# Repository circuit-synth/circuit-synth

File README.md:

# circuit-synth

Define electronic circuits in Python and generate KiCad projects (schematic +
PCB) from them.

> **This is a development fork** of [circuit-synth](https://github.com/circuit-synth/circuit-synth).
> It is not published to PyPI under this fork; install it locally (below).
> Everything documented here is verified against the code in `src/circuit_synth/`.

## What it does

You describe components and their connections in Python; circuit-synth produces
a complete KiCad project. Because the design is code, it is diffable,
version-controlled, and composable — subcircuits are just functions you call.

```python
from circuit_synth import circuit, Component, Net

@circuit(name="Power_Supply")
def power_supply(vin, vout, gnd):
    """5V -> 3.3V linear regulator with decoupling."""
    reg = Component(
        symbol="Regulator_Linear:AMS1117-3.3",
        ref="U",
        footprint="Package_TO_SOT_SMD:SOT-223-3_TabPin2",
    )
    cin  = Component(symbol="Device:C", ref="C", value="10uF")
    cout = Component(symbol="Device:C", ref="C", value="22uF")

    reg["VI"] += vin
    reg["VO"] += vout
    reg["GND"] += gnd
    cin[1]  += vin;  cin[2]  += gnd
    cout[1] += vout; cout[2] += gnd

@circuit(name="Main")
def main():
    vbus, vcc, gnd = Net("VBUS"), Net("VCC_3V3"), Net("GND")
    power_supply(vbus, vcc, gnd)

if __name__ == "__main__":
    main().generate_kicad_project("my_board")   # -> my_board/*.kicad_sch, *.kicad_pcb
```

## Install (development fork)

```bash
git clone <this fork's url> circuit-synth
cd circuit-synth
uv sync                     # create the environment from uv.lock
uv run pytest               # sanity-check the install
```

Requirements:
- Python 3.12+
- `uv` (environment/build; the project uses setuptools + uv, not poetry)
- A KiCad install with `kicad-cli` on PATH. The fork's active work targets
  KiCad 10; `kicad-cli` is used for BOM/PDF/Gerber export.

## Core API

Exported from `circuit_synth`: `circuit`, `Component`, `Net`, `Pin`, `Circuit`.

- `Component(symbol=..., ref=..., footprint=..., value=..., **fields)` — a KiCad
  symbol instance. Extra keywords become component fields (used in the BOM).
- `Net("NAME")` — an electrical net. Connect a pin with `component["PIN"] += net`
  (named) or `component[1] += net` (numbered).
- `@circuit(name=...)` — decorates a function into a circuit; call other
  `@circuit` functions inside it to build hierarchy.

### Generation and manufacturing outputs

Methods on the circuit object returned by a `@circuit` function:

```python
c = main()

c.generate_kicad_project(
    "my_board",
    generate_pcb=True,                 # also lay out a .kicad_pcb
    placement_algorithm="hierarchical",# or "simple"
    force_regenerate=False,            # True discards manual KiCad edits
    update_source_refs=None,           # see "Reference rewriting"
)

c.generate_bom("my_board")            # CSV BOM (kwargs: output_file, group_by, exclude_dnp, ...)
c.generate_pdf_schematic("my_board")  # PDF (kwargs: black_and_white, pages, ...)
c.generate_gerbers("my_board")        # Gerber + drill files
```

BOM/PDF/Gerber export shells out to KiCad's `kicad-cli`. See
[docs/BOM_EXPORT.md](docs/BOM_EXPORT.md), [docs/PDF_EXPORT.md](docs/PDF_EXPORT.md),
[docs/GERBER_EXPORT.md](docs/GERBER_EXPORT.md).

### Reference rewriting

When references are finalized during generation (e.g. `ref="C"` becomes
`ref="C1"`), circuit-synth can write the finalized refs back into your Python
source file, so repeated generations stay consistent. Controlled by
`update_source_refs` (default `None` = auto-update unless `force_regenerate=True`;
pass `True`/`False` to force it). It rewrites `ref=` assignments only and leaves
comments/docstrings alone.

### Round-trip (KiCad <-> Python)

Both directions exist as CLI tools: `python-to-kicad` and `kicad-to-python`. You
can generate from Python, edit in KiCad, and import back.

## Starting a project

```bash
uv run cs-new-project my_board     # scaffold a project (starter circuit + Claude tooling)
cd my_board
uv run python circuit-synth/main.py   # generate the KiCad files
```

`cs-new-project` copies the packaged `example_project` template (a `circuit-synth/`
source folder, a `.claude/` design skill, and `tools/find_symbol.py`).
`cs-bootstrap` does the same and can run `main.py` for you in one step.

## Other capabilities (real, optional)

These exist in the package; most need extra setup or network access, and are
peripheral to the core Python -> KiCad flow:

- **SPICE simulation** — `circuit.simulator()` exposes `operating_point()`,
  `ac_analysis()`, etc. (ngspice). See [docs/SIMULATION_SETUP.md](docs/SIMULATION_SETUP.md).
- **FMEA report** — `cs-fmea my_circuit.py` generates a reliability report. See
  [docs/FMEA_GUIDE.md](docs/FMEA_GUIDE.md).
- **Component sourcing** — JLCPCB/DigiKey/SnapEDA search via the `jlc-fast` CLI
  and `circuit_synth.manufacturing.find_parts(...)`. DigiKey/SnapEDA need API
  keys (`cs-setup-digikey-api`, `cs-setup-snapeda-api`); JLCPCB search needs
  network access.

## Claude Code integration

The design loop is driven by skills and tools (not custom slash commands):

- **`new-kicad-project` skill** — bootstrap a new project.
- **`design-circuit` skill** — the design → verify → generate loop, including
  symbol/footprint lookup via `tools/find_symbol.py`.
- **kicad-sch-api MCP server** — programmatic read/write of `.kicad_sch` files.

Verify symbols/footprints with `tools/find_symbol.py` rather than trusting a
static list — names vary by KiCad version and are easy to get wrong.

## Development

```bash
uv run pytest                # tests
black src/ tests/            # format (also run by pre-commit)
isort src/ tests/
```

See [CLAUDE.md](CLAUDE.md) for the working policy (human-in-the-loop; commit
often; **no PyPI releases**) and the loop boundary contract, and
[docs/CONTRIBUTING.md](docs/CONTRIBUTING.md) / [docs/TESTING.md](docs/TESTING.md).

## Architecture

JSON is the canonical intermediate representation between Python and KiCad,
which makes the design text-based and round-trippable. See
[docs/ARCHITECTURE.md](docs/ARCHITECTURE.md) and
[docs/JSON_SCHEMA.md](docs/JSON_SCHEMA.md).

## License

MIT

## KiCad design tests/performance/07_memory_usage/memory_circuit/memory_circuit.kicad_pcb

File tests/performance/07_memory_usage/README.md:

# Test 07: Memory Usage Monitoring

Performance test for Monitor memory during generation.

```bash
pytest test_*.py -v
```

Performance threshold: 30.0s

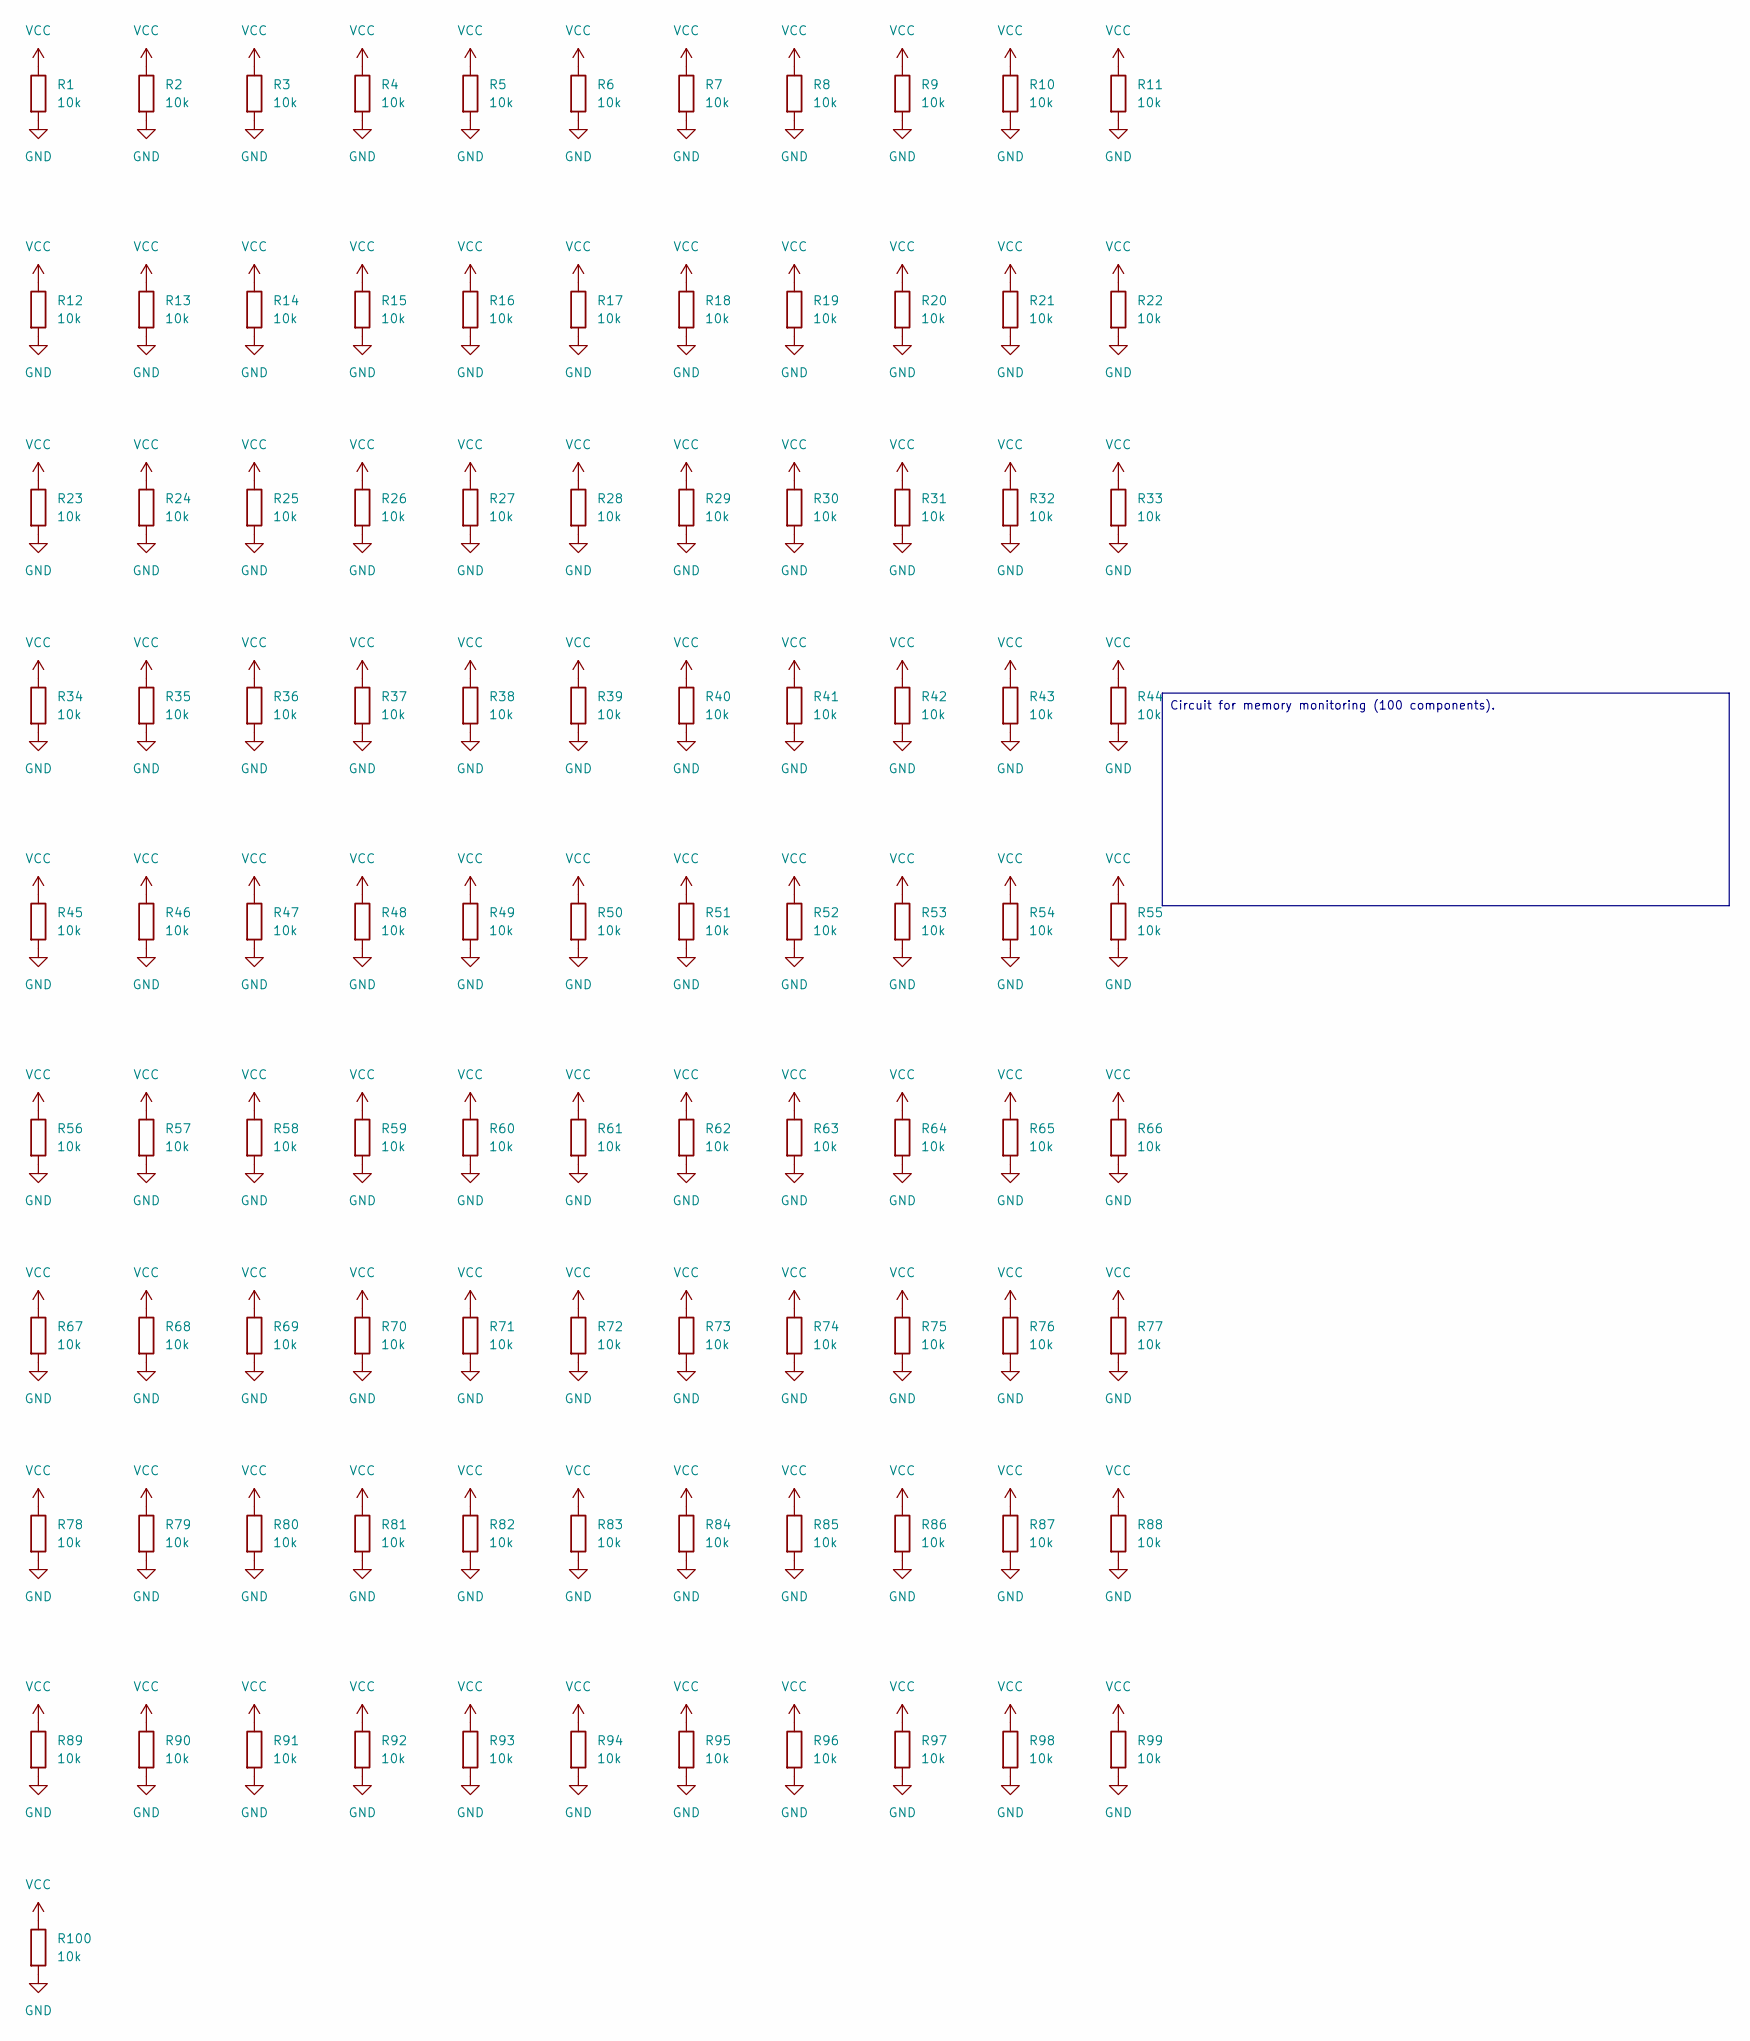
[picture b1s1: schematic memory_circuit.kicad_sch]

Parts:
R1, R2, R3, R4, R5, R6, R7, R8, R9, R10, R11, R12, R13, R14, R15, R16, R17, R18, R19, R20, R21, R22, R23, R24, R25, R26, R27, R28, R29, R30, R31, R32, R33, R34, R35, R36, R37, R38, R39, R40, R41, R42, R43, R44, R45, R46, R47, R48, R49, R50, R51, R52, R53, R54, R55, R56, R57, R58, R59, R60, R61, R62, R63, R64, R65, R66, R67, R68, R69, R70, R71, R72, R73, R74, R75, R76, R77, R78, R79, R80, R81, R82, R83, R84, R85, R86, R87, R88, R89, R90, R91, R92, R93, R94, R95, R96, R97, R98, R99, R100: 10k; R_0603_1608Metric

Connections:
GND: R1.2, R2.2, R3.2, R4.2, R5.2, R6.2, R7.2, R8.2, R9.2, R10.2, R11.2, R12.2, R13.2, R14.2, R15.2, R16.2, R17.2, R18.2, R19.2, R20.2, R21.2, R22.2, R23.2, R24.2, R25.2, R26.2, R27.2, R28.2, R29.2, R30.2, R31.2, R32.2, R33.2, R34.2, R35.2, R36.2, R37.2, R38.2, R39.2, R40.2, R41.2, R42.2, R43.2, R44.2, R45.2, R46.2, R47.2, R48.2, R49.2, R50.2, R51.2, R52.2, R53.2, R54.2, R55.2, R56.2, R57.2, R58.2, R59.2, R60.2, R61.2, R62.2, R63.2, R64.2, R65.2, R66.2, R67.2, R68.2, R69.2, R70.2, R71.2, R72.2, R73.2, R74.2, R75.2, R76.2, R77.2, R78.2, R79.2, R80.2, R81.2, R82.2, R83.2, R84.2, R85.2, R86.2, R87.2, R88.2, R89.2, R90.2, R91.2, R92.2, R93.2, R94.2, R95.2, R96.2, R97.2, R98.2, R99.2, R100.2
VCC: R1.1, R2.1, R3.1, R4.1, R5.1, R6.1, R7.1, R8.1, R9.1, R10.1, R11.1, R12.1, R13.1, R14.1, R15.1, R16.1, R17.1, R18.1, R19.1, R20.1, R21.1, R22.1, R23.1, R24.1, R25.1, R26.1, R27.1, R28.1, R29.1, R30.1, R31.1, R32.1, R33.1, R34.1, R35.1, R36.1, R37.1, R38.1, R39.1, R40.1, R41.1, R42.1, R43.1, R44.1, R45.1, R46.1, R47.1, R48.1, R49.1, R50.1, R51.1, R52.1, R53.1, R54.1, R55.1, R56.1, R57.1, R58.1, R59.1, R60.1, R61.1, R62.1, R63.1, R64.1, R65.1, R66.1, R67.1, R68.1, R69.1, R70.1, R71.1, R72.1, R73.1, R74.1, R75.1, R76.1, R77.1, R78.1, R79.1, R80.1, R81.1, R82.1, R83.1, R84.1, R85.1, R86.1, R87.1, R88.1, R89.1, R90.1, R91.1, R92.1, R93.1, R94.1, R95.1, R96.1, R97.1, R98.1, R99.1, R100.1

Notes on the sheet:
Circuit for memory monitoring (100 components).

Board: 2 copper layers, 100 parts (0 on the bottom side), 2 nets, no tracks yet.

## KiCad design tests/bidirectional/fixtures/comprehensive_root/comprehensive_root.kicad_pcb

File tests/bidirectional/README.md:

# Bidirectional Sync Tests

Comprehensive test suite for validating bidirectional synchronization between Python circuit definitions and KiCad schematics.

## Quick Start

**Run all passing tests:**
```bash
pytest tests/bidirectional/component_crud_root/*/test_*.py tests/bidirectional/net_crud_root/*/test_*.py -v
```

**Manual verification checklist:**
See [MANUAL_TEST_CHECKLIST.md](./MANUAL_TEST_CHECKLIST.md) for detailed manual testing instructions.

## Current Status

**Completed & Passing**: 8/45 tests (18%)
- ✅ Tests 10-13: Component CRUD (Root Sheet)
- ✅ Tests 14-17: Net CRUD (Root Sheet)

**In Progress**: Tests 18-25 (Hierarchical CRUD operations)

## Philosophy

**Simple, Automated, Comprehensive**

- **One test = One scenario** - Each test demonstrates one specific CRUD operation
- **Automated verification** - Tests use kicad-sch-api for programmatic validation
- **Position preservation** - Tests verify component positions survive regeneration
- **Self-contained** - Each test directory has circuit + test + README

## Test Coverage Plan (45 Tests Total)

### Component CRUD - Root Sheet (Tests 10-13) ✅
- Test 10: Add component
- Test 11: Update component value
- Test 12: Rename component (update ref)
- Test 13: Delete component

### Net CRUD - Root Sheet (Tests 14-17) ✅
- Test 14: Add net
- Test 15: Update net connection
- Test 16: Rename net
- Test 17: Delete net

### Component CRUD - Hierarchical (Tests 18-21) 🏗️
- Test 18: Add component in subcircuit
- Test 19: Update component value in subcircuit
- Test 20: Rename component in subcircuit
- Test 21: Delete component in subcircuit

### Net CRUD - Hierarchical (Tests 22-25) 🏗️
- Test 22: Add net in subcircuit
- Test 23: Update net in subcircuit
- Test 24: Rename net in subcircuit
- Test 25: Delete net in subcircuit

### Sheet CRUD (Tests 26-29) 📋
- Test 26: Add hierarchical sheet
- Test 27: Update sheet properties
- Test 28: Rename sheet
- Test 29: Delete sheet

### Label CRUD (Tests 30-33) 📋
- Test 30: Add hierarchical label
- Test 31: Update label properties
- Test 32: Rename label
- Test 33: Delete label

### Power Symbol CRUD (Tests 34-37) 📋
- Test 34: Add power symbol
- Test 35: Change power symbol type
- Test 36: Rename power net
- Test 37: Delete power symbol

### Cross-Hierarchy Operations (Tests 38-41) 📋
- Test 38: Connect across sheets
- Test 39: Modify cross-sheet connection
- Test 40: Move component between sheets
- Test 41: Propagate changes up/down hierarchy

### Bulk Operations (Tests 42-45) 📋
- Test 42: Add multiple components
- Test 43: Update multiple components
- Test 44: Delete multiple components
- Test 45: Complex multi-operation workflow

## Test Structure

Each test follows the **one-folder-per-test** pattern:

```
tests/bidirectional/
├── component_crud_root/
│   ├── 10_sync_component_root_create/
│   │   ├── comprehensive_root.py      # Circuit definition
│   │   ├── test_add_component.py      # Automated test
│   │   └── README.md                  # Manual instructions
│   ├── 11_sync_component_root_update_value/
│   ├── 12_sync_component_root_update_ref/
│   └── 13_sync_component_root_delete/
├── net_crud_root/
│   ├── 14_sync_net_root_create/
│   ├── 15_sync_net_root_update/
│   ├── 16_sync_net_root_rename/
│   └── 17_sync_net_root_delete/
├── component_crud_hier/
│   └── 18-21...
├── net_crud_hier/
│   └── 22-25...
└── MANUAL_TEST_CHECKLIST.md           # Manual verification checklist
```

## Running Tests

### Automated Tests (Recommended)

Run all passing tests:
```bash
pytest tests/bidirectional/component_crud_root/*/test_*.py \
       tests/bidirectional/net_crud_root/*/test_*.py -v
```

Run specific test:
```bash
pytest tests/bidirectional/component_crud_root/10_sync_component_root_create/test_add_component.py -v
```

Keep test outputs for inspection:
```bash
pytest tests/bidirectional/component_crud_root/10_sync_component_root_create/test_add_component.py -v --keep-output
```

### Manual Testing

For manual verification in KiCad:

1. Navigate to test directory:
   ```bash
   cd tests/bidirectional/component_crud_root/10_sync_component_root_create
   ```

2. Generate circuit:
   ```bash
   uv run comprehensive_root.py
   ```

3. Open in KiCad:
   ```bash
   open comprehensive_root/comprehensive_root.kicad_pro
   ```

4. Follow README.md instructions to perform the test operation

## Test Verification

Each test verifies:
- ✅ Circuit generates without errors
- ✅ Component positions preserved across regeneration
- ✅ Component values preserved
- ✅ Net connections preserved
- ✅ Power symbols preserved
- ✅ Modified elements updated correctly

Tests use **kicad-sch-api 0.4.5+** for programmatic KiCad schematic verification.

## Key Testing Patterns

### Position Preservation Test

```python
# STEP 1: Generate initial circuit
result = subprocess.run(["uv", "run", "comprehensive_root.py"])
sch = Schematic.load("comprehensive_root/comprehensive_root.kicad_sch")

# Store positions
r1_pos_before = r1.position

# STEP 2: Modify circuit (e.g., change R1 value)
modify_circuit_code()

# STEP 3: Regenerate
result = subprocess.run(["uv", "run", "comprehensive_root.py"])
sch_after = Schematic.load("comprehensive_root/comprehensive_root.kicad_sch")

# STEP 4: Verify position preserved
assert r1_after.position.x == r1_pos_before.x
assert r1_after.position.y == r1_pos_before.y
```

## Legacy Tests

Old tests are archived in `_archive_legacy_tests/` for reference but are not actively maintained.

## Contributing

When adding new tests:
1. Follow the one-folder-per-test pattern
2. Include comprehensive_root.py (circuit), test_*.py (automated test), README.md (manual instructions)
3. Use kicad-sch-api for verification
4. Test both automated pytest execution and manual KiCad verification
5. Update MANUAL_TEST_CHECKLIST.md

## Documentation

- **MANUAL_TEST_CHECKLIST.md** - Checkbox list for manual verification of all 45 tests
- **README.md** (this file) - Overview and quick reference
- **_archive_docs/** - Historical status documents (archived)

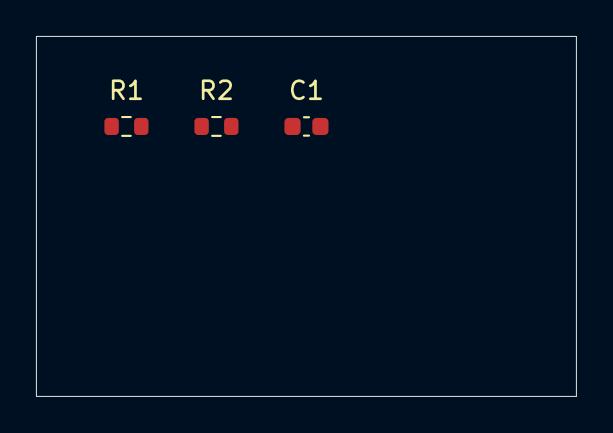
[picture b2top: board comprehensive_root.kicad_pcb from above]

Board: 2 copper layers, 30.0 x 20.0 mm, 3 parts (0 on the bottom side), 2 nets, no tracks yet.

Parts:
C1: 100nF; C_0603_1608Metric
R1: 10k; R_0603_1608Metric
R2: 4.7k; R_0603_1608Metric

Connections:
DATA: C1.1, R1.1
GND: C1.2, R2.2

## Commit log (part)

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2025-10-29 remove uneeded file
2025-10-29 fix: Fix failing bidirectional tests 19, 21, 24, 27, 33
    Fixed all 5 failing tests with API corrections and XFAIL markers:
    **Test Fixes:**
    - Test 19 (swap_component_type): Fixed API - use lib_id instead of symbol
    - Marked as XFAIL - synchronizer doesn't support changing component symbols
    - Test 21 (multi_unit_components): Fixed slice notation - use loop instead
    - Marked as XFAIL - netlist exporter doesn't handle all multi-unit pins
2025-10-29 chore: Remove monkey-patch and update kicad-sch-api to v0.4.3
    The Symbol comparison bug is now fixed in kicad-sch-api v0.4.3,
    so the temporary monkey-patch is no longer needed.
    Changes:
    - Update pyproject.toml: kicad-sch-api>=0.4.2 → >=0.4.3
    - Remove src/circuit_synth/__init__.py: monkey-patch import
    - Remove src/circuit_synth/kicad/kicad_sch_api_patch.py
2025-10-29 fix: Correct hierarchical label justify for 270° rotation (#380)
    Fixed hierarchical labels at 270° rotation to use "left" justification
    instead of "right", matching KiCad's expected text rendering behavior.
    Problem:
    - Initial generation used justify="right" for 270° labels
    - Synchronizer used kicad-sch-api which has different justify defaults
    - Labels appeared upside-down when added by synchronizer
2025-10-29 fix: Add power symbol placement during synchronization (#394) (#395)
    * remove kicad files
    * fix: Add power symbol placement during synchronization (#394)
    When adding a power net (VCC, GND, etc.) to an existing circuit via
    synchronization, the synchronizer now correctly places power symbol
    components instead of only adding hierarchical labels.
    Changes:
2025-10-29 test: Update test 16 to expect VCC power symbol component
    - Update assertion to expect 2 components (R1 + VCC power symbol)
    - Add validation that VCC power symbol is created during sync
    - Remove hierarchical label check (power symbols replace labels)
    - Test now correctly validates power symbol synchronizer behavior
2025-10-29 test: Mark test 12 as manually validated; document label orientation issue (#403)
2025-10-30 test: Mark test 15 as manually validated - net split works correctly
2025-10-30 test: Mark test 17 as manually validated - ground symbol (GND) working
2025-10-30 test: Mark test 20 as manually validated - rotation preservation works (property text issue #401 documented)
2025-10-30 docs: Record test 33 manual validation - 8-bit bus connections
    - Test 33 manually validated and passes
    - All 8 data lines (D0-D7) visible with hierarchical labels
    - Netlist correctly shows MCU1 ↔ MEM1 connections for all 8 nets
    - Test also validates modification workflow (changing D0 to use BUF1)
    - Progress: 25 of 66 tests (38%)
2025-10-30 refactor: Use Python loops in tests 34 and 68 - demonstrate circuit-synth advantage
    Changes:
    - Test 34 (ten_resistors.py): Replaced 87 lines of manual component definitions
    with 5-line loop (for i in range(1, 11))
    - To add 10 more: Just change range(1, 11) to range(1, 21)
    - Demonstrates Python advantage: no copy-paste needed!
    - Test 68 (growing_circuit.py): Replaced 50 lines of commented component code
2025-10-30 refactor: Remove post-save hierarchical path workaround, use kicad-sch-api 0.4.5+ instance preservation
    - Updated kicad-sch-api dependency to >= 0.4.5
    - Removed post-save path correction workaround from synchronizer.py (lines 1281-1329)
    - Cleaned up debug print statements from instance_utils.py and component_manager.py
    - kicad-sch-api v0.4.5 now properly preserves user-set hierarchical instances through save/load cycles
    Fixes #406 - Components in hierarchical child sheets now display correct reference designators
2025-10-30 docs: Remove IMPLEMENTATION_SUMMARY.md (details in PR description)
2025-10-30 docs: Update bidirectional test summary with Issue #406 resolution
    - Added comprehensive Issue #406 fix documentation
    - Documented kicad-sch-api v0.4.5 release and PyPI publication
    - Updated test suite status to reflect hierarchical sheets working
    - Confirmed end-to-end validation with Test 22
    - All component references displaying correctly in hierarchical designs
2025-10-31 fix: Restore 'uv run' prefix for cs-new-project commands
    Restores uv run prefix for consistency:
    - Line 132: uv run cs-new-project my_first_board
    - Line 172: uv run cs-new-project my_project
    - Line 712: uv run cs-new-project
    All commands now consistently use 'uv run' for both cs-new-project
    and python main.py, maintaining the uv-first workflow throughout
2025-10-31 style: Apply Black formatting to component_manager.py
2025-10-31 refactor: Update Test 59 to use modern declarative @circuit syntax
    Changes:
    - Use @circuit(name=...) decorator pattern for both main and subcircuit
    - Components auto-added to current circuit context (no explicit add_component)
    - Subcircuit invoked via function call: spi_driver(data_in)
    - Use get_current_circuit() to access root circuit
    - Cleaner, more Pythonic declarative API
2025-10-31 test: Refactor Tests 38 & 59 to modern syntax + document critical bugs (#431)
    Refactored test fixtures and documentation:
    - Test 38 (empty subcircuit): Modern @circuit decorator syntax
    - Test 59 (hierarchical pin rename): Modern @circuit decorator syntax
    - Updated all documentation with consistent Generate/Sync terminology
    - Updated BIDIRECTIONAL_TEST_SUMMARY.md with test session results
    Manual testing session results:
2025-10-31 fix: Update PCB sync test helpers to work with kicad_pcb_api Footprint objects
    Updated helper methods to properly handle kicad_pcb_api's Footprint objects:
    - _find_footprint_by_ref(): Added direct reference attribute check before falling back to properties search
    - _get_footprint_position(): Handle Point objects with x/y attributes instead of array-based 'at' values
    - _set_footprint_position(): Properly update Point object coordinates instead of dict-based 'at' values
    This fixes 5 of 7 PCB synchronization tests. Remaining 2 tests require:
    1. Component removal synchronization (delete footprints for removed components)
2025-10-31 fix: Use .values() when iterating over circuit.components dict
    - circuit.components is now a dict, requires .values() for iteration
    - Fixed 5 test files that were iterating directly over components
    - Resolves 'AttributeError: str object has no attribute ref' errors
    Tests affected:
    - test_45_import_power_symbols.py (now xfail as expected)
    - test_phase0_json_canonical.py
2025-10-31 fix: Update Python version requirement from 3.9+ to 3.12+ in documentation (#447)
    - Update README.md: Python 3.9+ → Python 3.12+
    - Update docs/installation.rst: Python 3.9+ → Python 3.12+
    - Update docs/BOM_EXPORT.md: Python 3.8+ → Python 3.12+
    - Update docs/PDF_EXPORT.md: Python 3.8+ → Python 3.12+
    - Update docs/GERBER_EXPORT.md: Python 3.8+ → Python 3.12+
    Aligns documentation with pyproject.toml requirement (>=3.12).
2025-11-03 fix: Implement Phase 1 production-ready improvements
    Phase 1.1: Idempotent worktree creation
    - Add ensure_worktree() method to handle existing worktrees gracefully
    - Add _worker_is_running() helper to detect stale worktrees
    - Replace create_worktree() calls with ensure_worktree()
    - Automatically remove stale worktrees when worker has exited
    - Prevents "already exists" errors on repeated runs
2025-11-03 fix: Power symbol label positioning during sync (#476)
    Problem: Power symbols created during bidirectional sync had Value
    labels positioned incorrectly. VCC labels appeared below symbols
    instead of above.
    Root Cause: synchronizer.py was missing the Value property position
    adjustment code that already exists in schematic_writer.py.
    Solution: Added property position adjustment in synchronizer.py
2025-11-03 docs: Add BLOCKED.md for issue #456 - cannot locate dashboard code
2025-11-03 docs: Block issue #455 - belongs in TAC repository
    Issue #455 requests dashboard monitoring features but this worktree is
    for circuit-synth library (KiCad generator). Dashboard code exists in
    separate circuit-synth-tac repository at /home/shane/Desktop/circuit-synth-tac/.
    Need guidance on:
    - How to access TAC repository for this work
    - Whether to transfer issue to TAC repo
2025-11-03 docs: Mark gh-450 as completed (duplicate work detected)
    Issue #450 was already completed on worktree auto/w-b5662c in commit ce870fd.
    PR #481 has been created and is open for review.
    This worktree detected the duplicate work and is documenting it for coordination purposes.
    Fixes #450
2025-11-03 chore: Update tasks.md - mark gh-469 as completed
    - Moved gh-469 from Pending to Completed Today
    - Updated timestamp
    - Added completion details (commit, PR, status)
2025-11-03 docs: Add worker completion report for gh-450
2025-11-03 chore: Ignore session-specific documentation files
2025-11-03 fix: Restore comprehensive_root.py to proper initial state for tests
    - Comment out R2 component and connections (tests expect this initial state)
    - Fix test_12 to use correct output directory with special project name
    - Tests were failing because R2 was uncommented from manual testing
    The tests add R2 during sync to verify Issue #479 fix.
2025-11-03 fix: Reconcile pin connections for newly added components during sync (#489) (#491)
    **Problem:**
    When components were added during bidirectional sync, they appeared in the
    schematic but WITHOUT hierarchical labels or power symbols on their pins.
    This left connections incomplete - users had to manually wire new components.
    **Root Cause:**
    `_reconcile_pin_connections()` only processed components in the `matches` dict
2025-11-03 docs: Add incident report for spawn loop fix
    Comprehensive documentation of:
    - Symptoms and timeline
    - Root cause analysis
    - Fix implementation
    - Verification results
    - Impact assessment
2025-11-03 fix: Correct Claude model names to claude-sonnet-4-5 and claude-haiku-4-5
    - Updated all prompts to use correct API model names
    - Removed max_tokens limits (let Claude decide based on task)
    - PR Creator uses Haiku 4-5 (cheaper, faster for simple task)
    - All other stages use Sonnet 4-5 (best coding model)
2025-11-04 test: Add comprehensive Phase 1 test suite
    Self-testing script that validates all PostgreSQL functionality:
    Tests (9 total):
    ✓ PostgreSQL connection
    ✓ All 7 tables exist
    ✓ Task creation and auto-cost rollup triggers
    ✓ Helper agent tracking with cost aggregation
2025-11-04 fix: Remove root API endpoint to allow static file serving
    The @app.get("/") endpoint was intercepting requests before the
    StaticFiles mount could serve index.html. Removed the root endpoint
    so the dashboard frontend is now properly served at /.
    API endpoints remain accessible at /api/* and documentation at /docs.
    Verified:
    - http://localhost:8001/ serves index.html
2025-11-05 docs: Comprehensive plan to complete TAC-X system
    Created detailed analysis and implementation plan for remaining work:
    Current State:
    ✅ Worker executes Claude CLI successfully
    ✅ Tools working (Bash, Read, Grep, Glob, Write)
    ✅ plan.md created (12KB, comprehensive)
    ✅ Token tracking functional
2025-11-17 chore: Clean up debug and temporary files before release
2025-11-18 chore: Remove all TAC-related files and references
    Removed TAC (Task Autonomous Coordinator) content that was accidentally
    added from another project:
    - Deleted 15 TAC-related documentation, design, and tool files
    - Removed TAC references from .gitignore, CLAUDE.md, and pyproject.toml
    - Deleted remote branch feat/tac-x-multi-stage-pipeline
    This content belonged in a separate autonomous development project
2026-01-09 chore: Bump version to 0.12.1
2026-03-07 fix: Add `reportlab` dependency to prevent `Warning: reportlab not installed. Install with: pip install reportlab` on first `uv run ...` call
